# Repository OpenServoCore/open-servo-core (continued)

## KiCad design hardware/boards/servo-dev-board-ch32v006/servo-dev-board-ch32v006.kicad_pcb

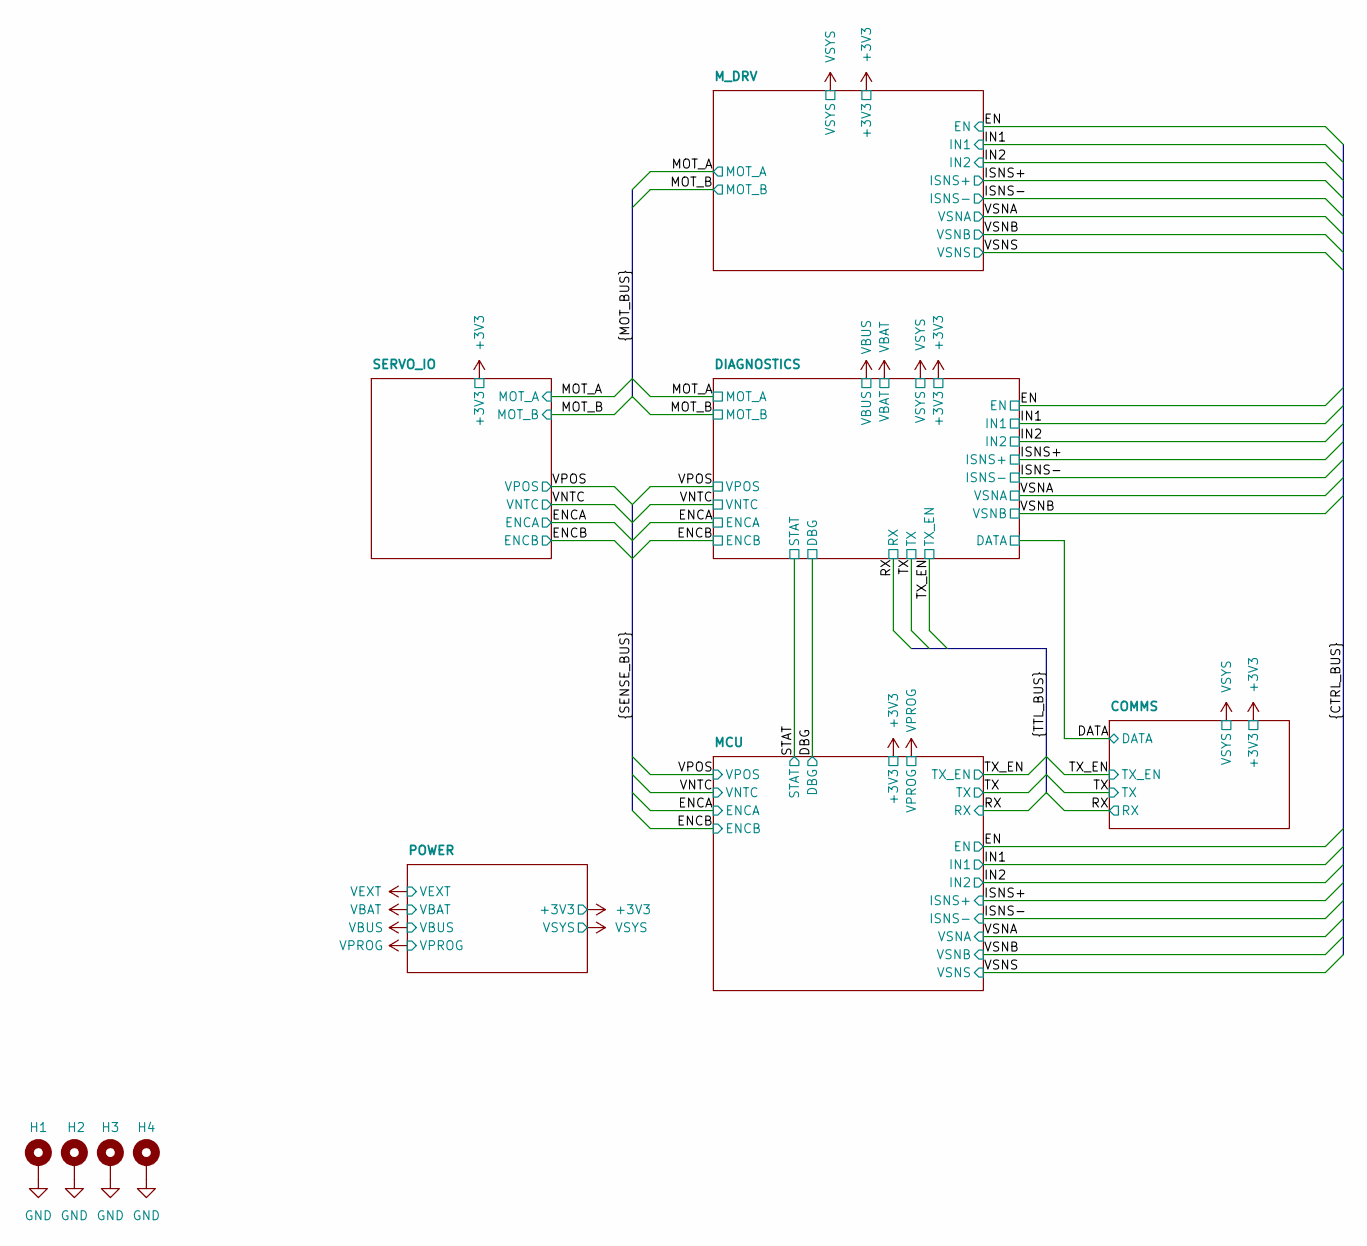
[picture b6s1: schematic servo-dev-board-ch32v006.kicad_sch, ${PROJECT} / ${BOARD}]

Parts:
H1, H2, H3, H4: MountingHole_Pad_MP; MountingHole_2.2mm_M2_ISO7380_Pad

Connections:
GND: H1.1 (1_1), H2.1 (1_1), H3.1 (1_1), H4.1 (1_1); also elsewhere on the board

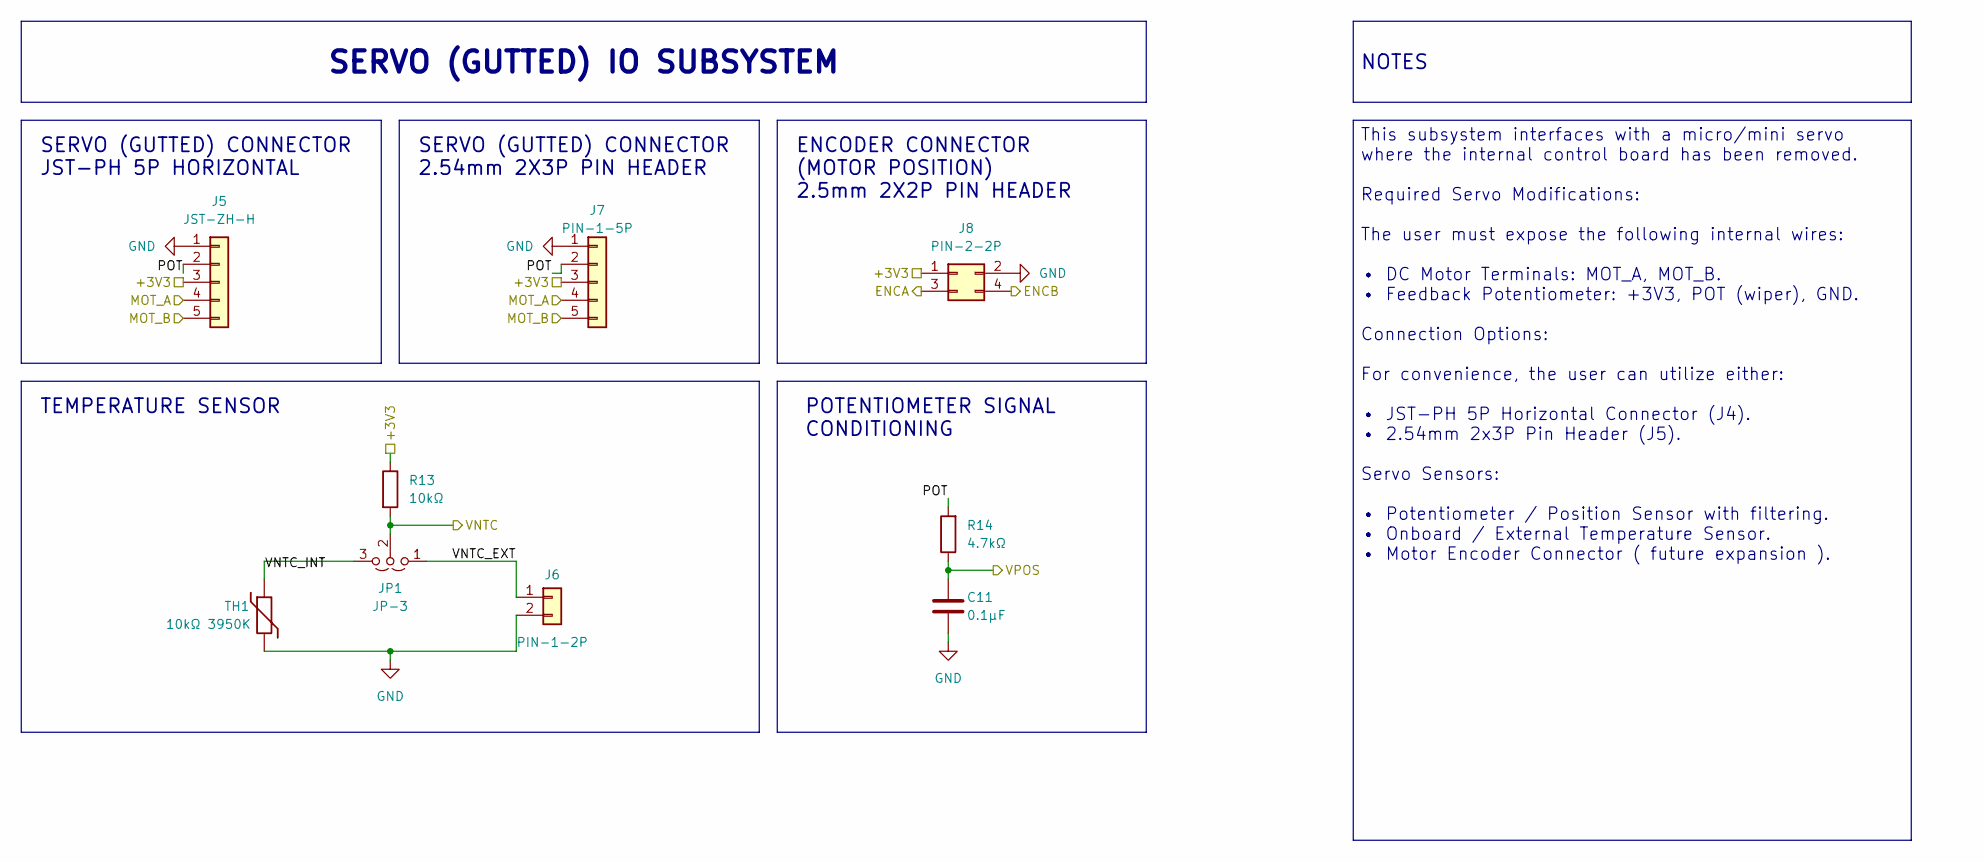
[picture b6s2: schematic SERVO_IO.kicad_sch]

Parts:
C11: 0.1µF; C_0805_2012Metric_Pad1.18x1.45mm_HandSolder; LCSC C28233
J5: JST-ZH-H; CONN-TH_S5B-ZR-LF-SN; JLC Type Extended
J6: PIN-1-2P; PinHeader_1x02_P2.54mm_Vertical; LCSC C492401
J7: PIN-1-5P; PinHeader_1x05_P2.54mm_Vertical; LCSC C42431812
J8: PIN-2-2P; PinHeader_2x02_P2.54mm_Vertical; LCSC C66690
JP1: JP-3; PinHeader_1x03_P2.54mm_Vertical; LCSC C41425293
R13: 10kΩ; R_0805_2012Metric_Pad1.20x1.40mm_HandSolder; LCSC C17414
R14: 4.7kΩ; R_0805_2012Metric_Pad1.20x1.40mm_HandSolder; LCSC C17673
TH1: 10kΩ 3950K; R_0805_2012Metric_Pad1.20x1.40mm_HandSolder; LCSC C95968

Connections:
+3V3: J5.3, J7.3, J8.1, R13.1; also elsewhere on the board
/ENCA: J8.3; also elsewhere on the board
/ENCB: J8.4; also elsewhere on the board
/MOT_A: J5.4, J7.4; also elsewhere on the board
/MOT_B: J5.5, J7.5; also elsewhere on the board
/SERVO_IO/POT: J5.2, J7.2, R14.2
/SERVO_IO/VNTC_EXT: J6.1, JP1.1 (A)
/SERVO_IO/VNTC_INT: JP1.3 (B), TH1.1
/VNTC: JP1.2 (C), R13.2; also elsewhere on the board
/VPOS: C11.1, R14.1; also elsewhere on the board
GND: C11.2, J5.1, J6.2, J7.1, J8.2, TH1.2; also elsewhere on the board

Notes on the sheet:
SERVO (GUTTED) CONNECTOR 2.54mm 2X3P PIN HEADER
ENCODER CONNECTOR (MOTOR POSITION) 2.5mm 2X2P PIN HEADER
TEMPERATURE SENSOR
POTENTIOMETER SIGNAL CONDITIONING
SERVO (GUTTED) CONNECTOR JST-PH 5P HORIZONTAL
This subsystem interfaces with a micro/mini servo where the internal control board has been removed. Required Servo Modifications: The user must expose the following internal wires: • DC Motor Terminals: MOT_A, MOT_B. • Feedback Potentiometer: +3V3, POT (wiper), GND. Connection Options: For conveni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
NOTES
SERVO (GUTTED) IO SUBSYSTEM

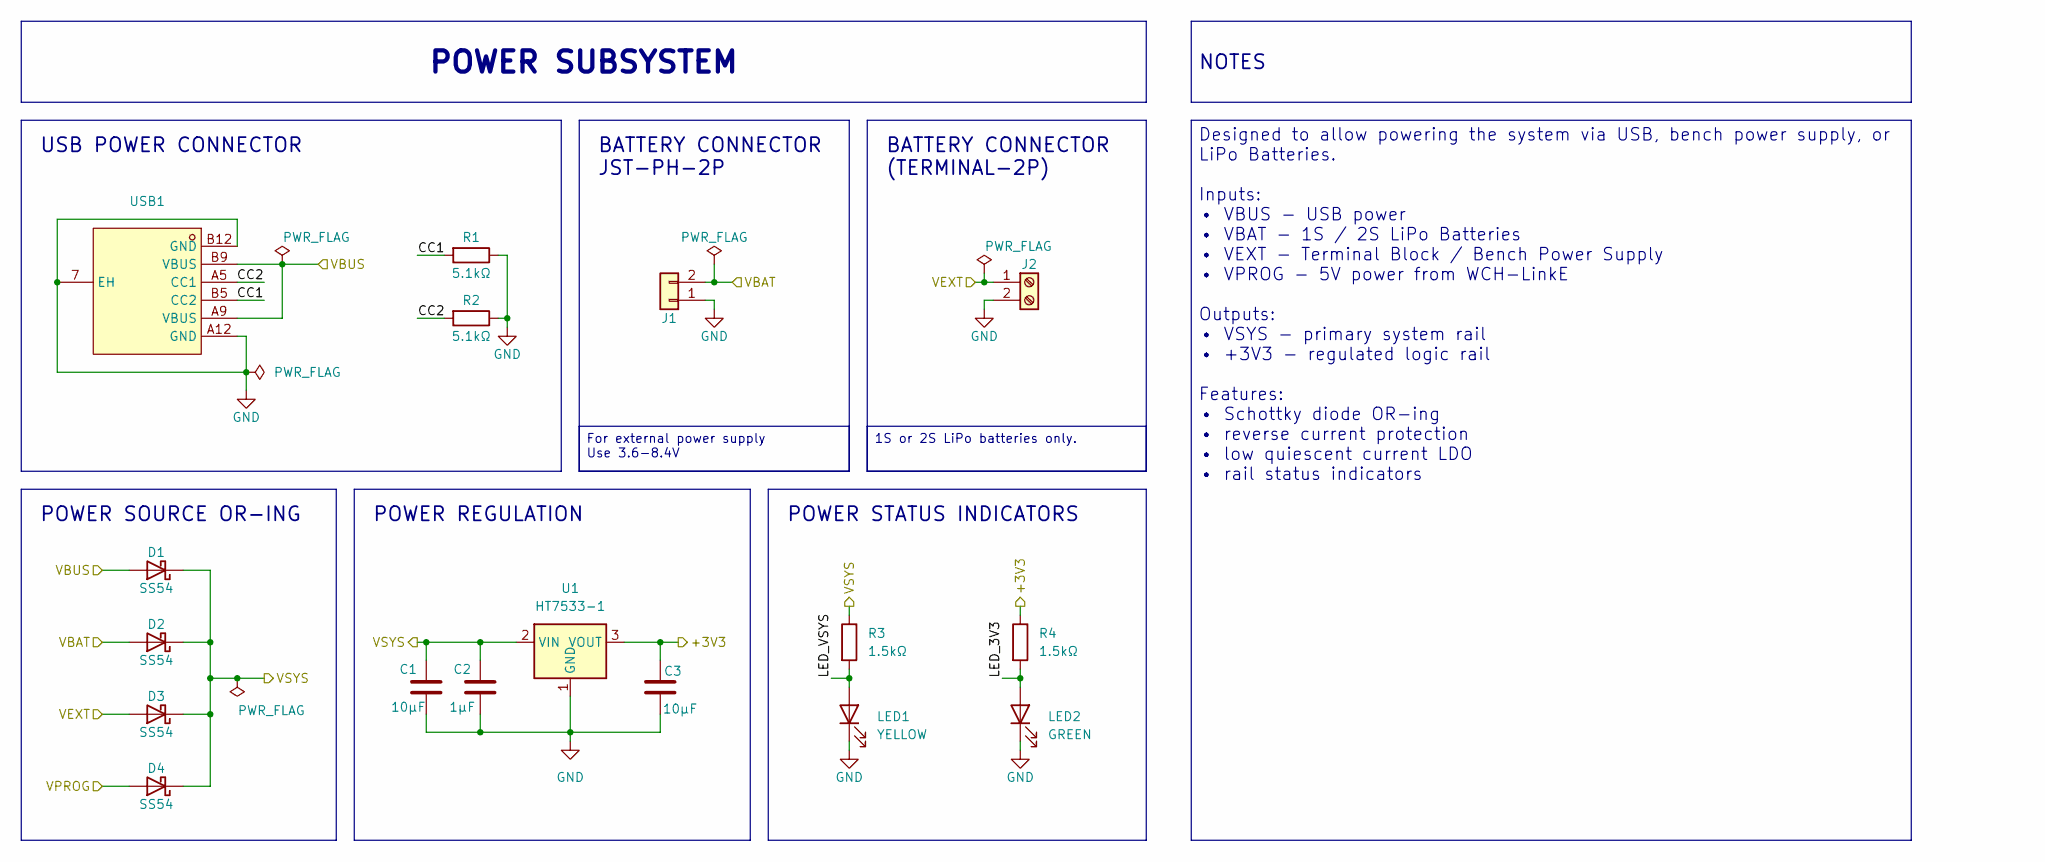
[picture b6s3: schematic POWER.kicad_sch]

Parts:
C1, C3: 10µF; C_0805_2012Metric_Pad1.18x1.45mm_HandSolder; LCSC C440198
C2: 1µF; C_0805_2012Metric_Pad1.18x1.45mm_HandSolder; LCSC C28323
D1, D2, D3, D4: SS54; D_SMA_Handsoldering; LCSC C22452
J1: JST-PH-H; CONN-TH_S2B-PH-K-S-LF-SN; LCSC C173752
J2: TERM; CONN-TH_2P-P5.00_WJ500V-5.08-2P; LCSC C8465
LED1: YELLOW; LED_0805_2012Metric; LCSC C2296
LED2: GREEN; LED_0805_2012Metric; LCSC C2297
R1, R2: 5.1kΩ; R_0805_2012Metric_Pad1.20x1.40mm_HandSolder; LCSC C27834
R3, R4: 1.5kΩ; R_0805_2012Metric_Pad1.20x1.40mm_HandSolder; LCSC C4310
U1: HT7533-1; SOT-89-3_Handsoldering; LCSC C14289
USB1: TYPE-C-H; TYPE-C-SMD_TYPE-C-6P-073; LCSC C668623

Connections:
+3V3: C3.1, R4.1, U1.3 (VOUT); also elsewhere on the board
/POWER/CC1: R1.2, USB1.B5 (CC2)
/POWER/CC2: R2.2, USB1.A5 (CC1)
/POWER/LED_3V3: LED2.2 (A), R4.2
/POWER/LED_VSYS: LED1.2 (A), R3.2
GND: C1.2, C2.2, C3.2, J1.1, J2.2, LED1.1 (K), LED2.1 (K), R1.1, R2.1, U1.1 (GND), USB1.7 (EH), USB1.A12 (GND), USB1.B12 (GND); also elsewhere on the board
VBAT: D2.2 (A), J1.2; also elsewhere on the board
VBUS: D1.2 (A), USB1.A9 (VBUS), USB1.B9 (VBUS); also elsewhere on the board
VEXT: D3.2 (A), J2.1
VPROG: D4.2 (A); also elsewhere on the board
VSYS: C1.1, C2.1, D1.1 (K), D2.1 (K), D3.1 (K), D4.1 (K), R3.1, U1.2 (VIN); also elsewhere on the board

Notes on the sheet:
BATTERY CONNECTOR JST-PH-2P
BATTERY CONNECTOR (TERMINAL-2P)
POWER REGULATION
POWER STATUS INDICATORS
USB POWER CONNECTOR
POWER SOURCE OR-ING
NOTES
Designed to allow powering the system via USB, bench power supply, or LiPo Batteries. Inputs: • VBUS - USB power • VBAT - 1S / 2S LiPo Batteries • VEXT - Terminal Block / Bench Power Supply • VPROG - 5V power from WCH-LinkE Outputs: • VSYS - primary system rail • +3V3 - regulated logic rail Feature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
POWER SUBSYSTEM
For external power supply Use 3.6-8.4V
1S or 2S LiPo batteries only.

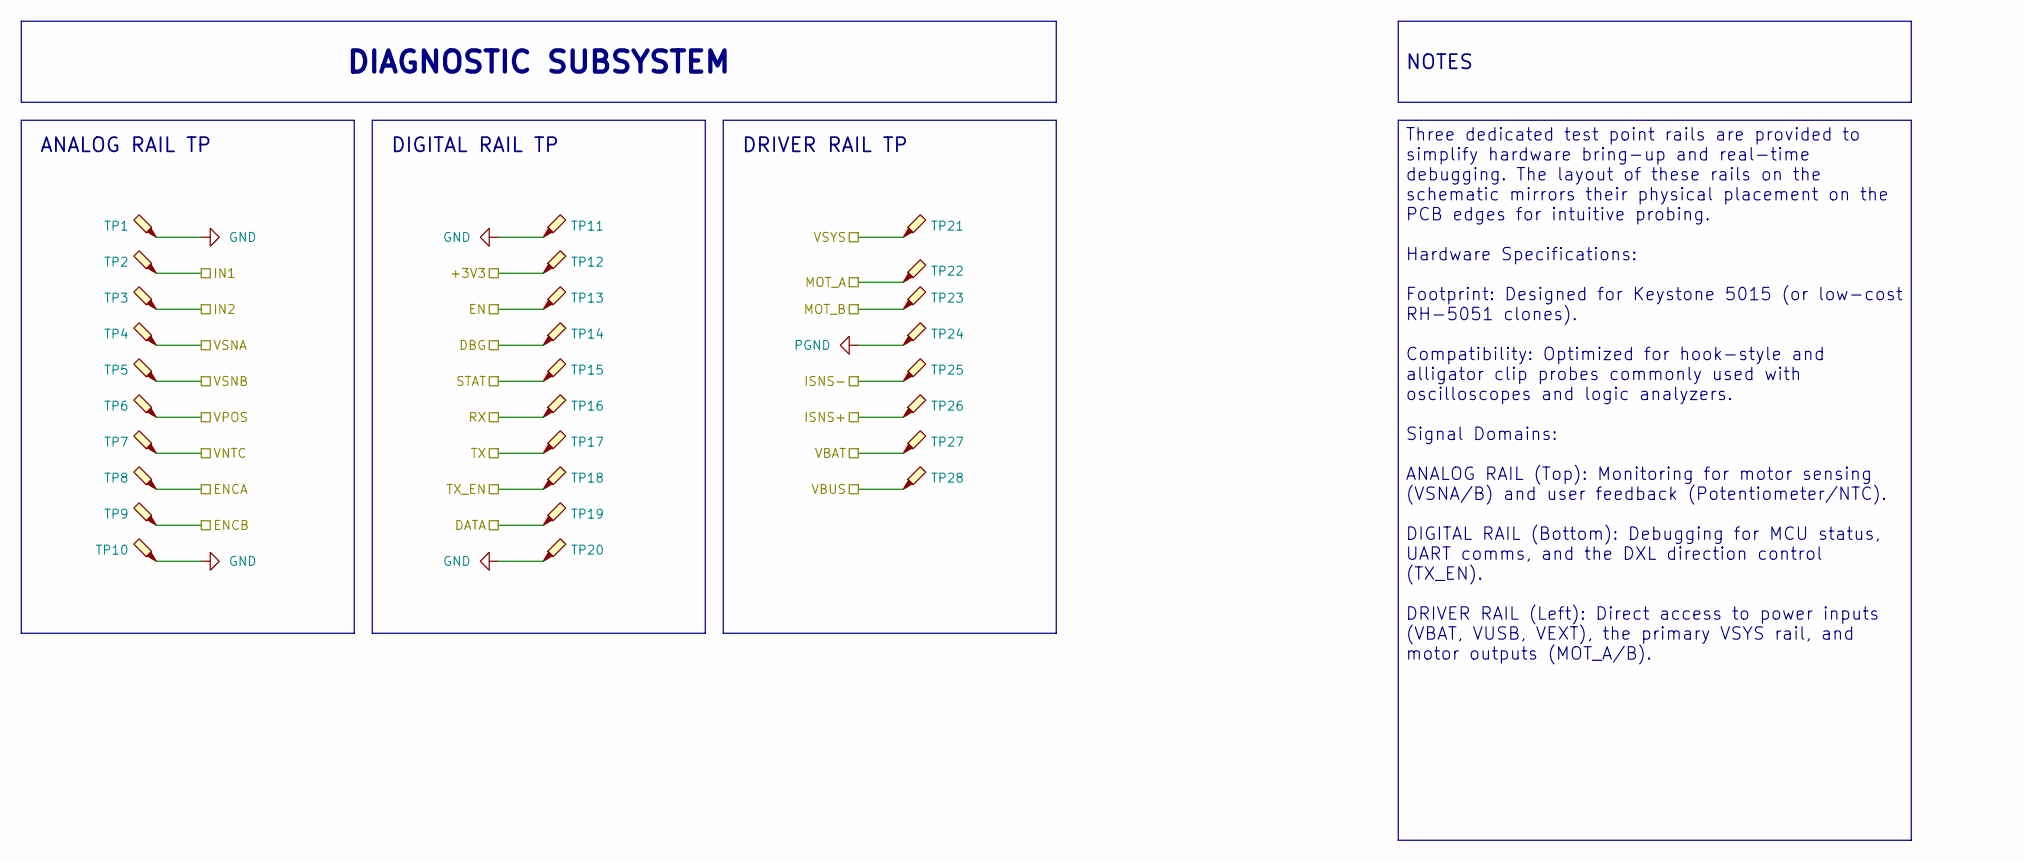
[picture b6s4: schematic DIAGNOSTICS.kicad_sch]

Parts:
TP1, TP2, TP3, TP4, TP5, TP6, TP7, TP8, TP9, TP10, TP11, TP12, TP13, TP14, TP15, TP16, TP17, TP18, TP19, TP20, TP21, TP22, TP23, TP24, TP25, TP26, TP27, TP28: TestPoint_Probe; TestPoint_Keystone_5015_Micro_Mini; LCSC C5199798

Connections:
+3V3: TP12.1 (1_1); also elsewhere on the board
/DATA: TP19.1 (1_1); also elsewhere on the board
/DBG: TP14.1 (1_1); also elsewhere on the board
/EN: TP13.1 (1_1); also elsewhere on the board
/ENCA: TP8.1 (1_1); also elsewhere on the board
/ENCB: TP9.1 (1_1); also elsewhere on the board
/IN1: TP2.1 (1_1); also elsewhere on the board
/IN2: TP3.1 (1_1); also elsewhere on the board
/ISNS+: TP26.1 (1_1); also elsewhere on the board
/ISNS-: TP25.1 (1_1); also elsewhere on the board
/MOT_A: TP22.1 (1_1); also elsewhere on the board
/MOT_B: TP23.1 (1_1); also elsewhere on the board
/RX: TP16.1 (1_1); also elsewhere on the board
/STAT: TP15.1 (1_1); also elsewhere on the board
/TX: TP17.1 (1_1); also elsewhere on the board
/TX_EN: TP18.1 (1_1); also elsewhere on the board
/VNTC: TP7.1 (1_1); also elsewhere on the board
/VPOS: TP6.1 (1_1); also elsewhere on the board
/VSNA: TP4.1 (1_1); also elsewhere on the board
/VSNB: TP5.1 (1_1); also elsewhere on the board
GND: TP1.1 (1_1), TP10.1 (1_1), TP11.1 (1_1), TP20.1 (1_1); also elsewhere on the board
PGND: TP24.1 (1_1); also elsewhere on the board
VBAT: TP27.1 (1_1); also elsewhere on the board
VBUS: TP28.1 (1_1); also elsewhere on the board
VSYS: TP21.1 (1_1); also elsewhere on the board

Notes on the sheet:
ANALOG RAIL TP
DRIVER RAIL TP
DIGITAL RAIL TP
DIAGNOSTIC SUBSYSTEM
NOTES
Three dedicated test point rails are provided to simplify hardware bring-up and real-time debugging. The layout of these rails on the schematic mirrors their physical placement on the PCB edges for intuitive probing. Hardware Specifications: Footprint: Designed for Keystone 5015 (or low-cost RH-505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

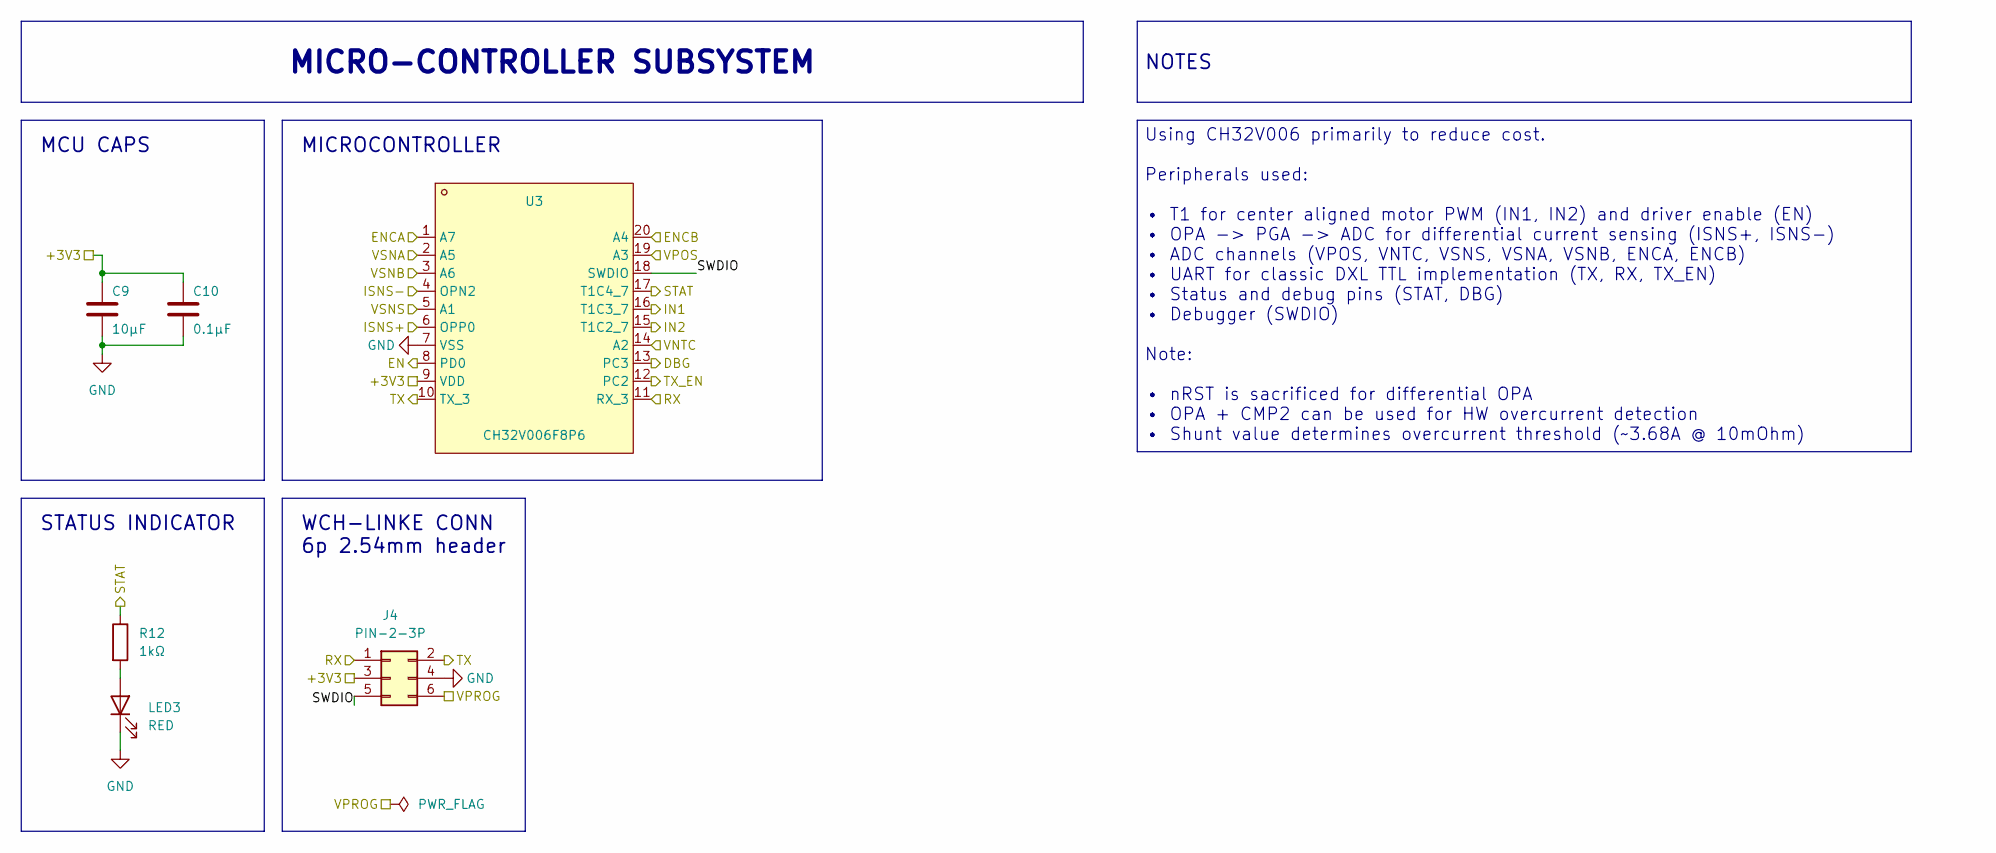
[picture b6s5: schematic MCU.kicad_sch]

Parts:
C9: 10µF; C_0805_2012Metric_Pad1.18x1.45mm_HandSolder; LCSC C440198
C10: 0.1µF; C_0805_2012Metric_Pad1.18x1.45mm_HandSolder; LCSC C28233
J4: PIN-2-3P; PinHeader_2x03_P2.54mm_Vertical; LCSC C65114
LED3: RED; LED_0805_2012Metric; LCSC C84256
R12: 1kΩ; R_0805_2012Metric_Pad1.20x1.40mm_HandSolder; LCSC C17513
U3: CH32V006F8P6; TSSOP-20_4.4x6.5mm_P0.65mm; LCSC C52753342

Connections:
+3V3: C9.1, C10.1, J4.3, U3.9 (VDD); also elsewhere on the board
/DBG: U3.13 (PC3); also elsewhere on the board
/EN: U3.8 (PD0); also elsewhere on the board
/ENCA: U3.1 (A7); also elsewhere on the board
/ENCB: U3.20 (A4); also elsewhere on the board
/IN1: U3.16 (T1C3_7); also elsewhere on the board
/IN2: U3.15 (T1C2_7); also elsewhere on the board
/ISNS+: U3.6 (OPP0); also elsewhere on the board
/ISNS-: U3.4 (OPN2); also elsewhere on the board
/MCU/SWDIO: J4.5, U3.18 (SWDIO)
/RX: J4.1, U3.11 (RX_3); also elsewhere on the board
/STAT: R12.1, U3.17 (T1C4_7); also elsewhere on the board
/TX: J4.2, U3.10 (TX_3); also elsewhere on the board
/TX_EN: U3.12 (PC2); also elsewhere on the board
/VNTC: U3.14 (A2); also elsewhere on the board
/VPOS: U3.19 (A3); also elsewhere on the board
/VSNA: U3.2 (A5); also elsewhere on the board
/VSNB: U3.3 (A6); also elsewhere on the board
/VSNS: U3.5 (A1); also elsewhere on the board
GND: C9.2, C10.2, J4.4, LED3.1 (K), U3.7 (VSS); also elsewhere on the board
unnamed: LED3.2 (A), R12.2
VPROG: J4.6; also elsewhere on the board

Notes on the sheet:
MCU CAPS
MICROCONTROLLER
STATUS INDICATOR
WCH-LINKE CONN 6p 2.54mm header
NOTES
Using CH32V006 primarily to reduce cost. Peripherals used: • T1 for center aligned motor PWM (IN1, IN2) and driver enable (EN) • OPA -> PGA -> ADC for differential current sensing (ISNS+, ISNS-) • ADC channels (VPOS, VNTC, VSNS, VSNA, VSNB, ENCA, ENCB) • UART for classic DXL TTL implementation (TX,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
MICRO-CONTROLLER SUBSYSTEM

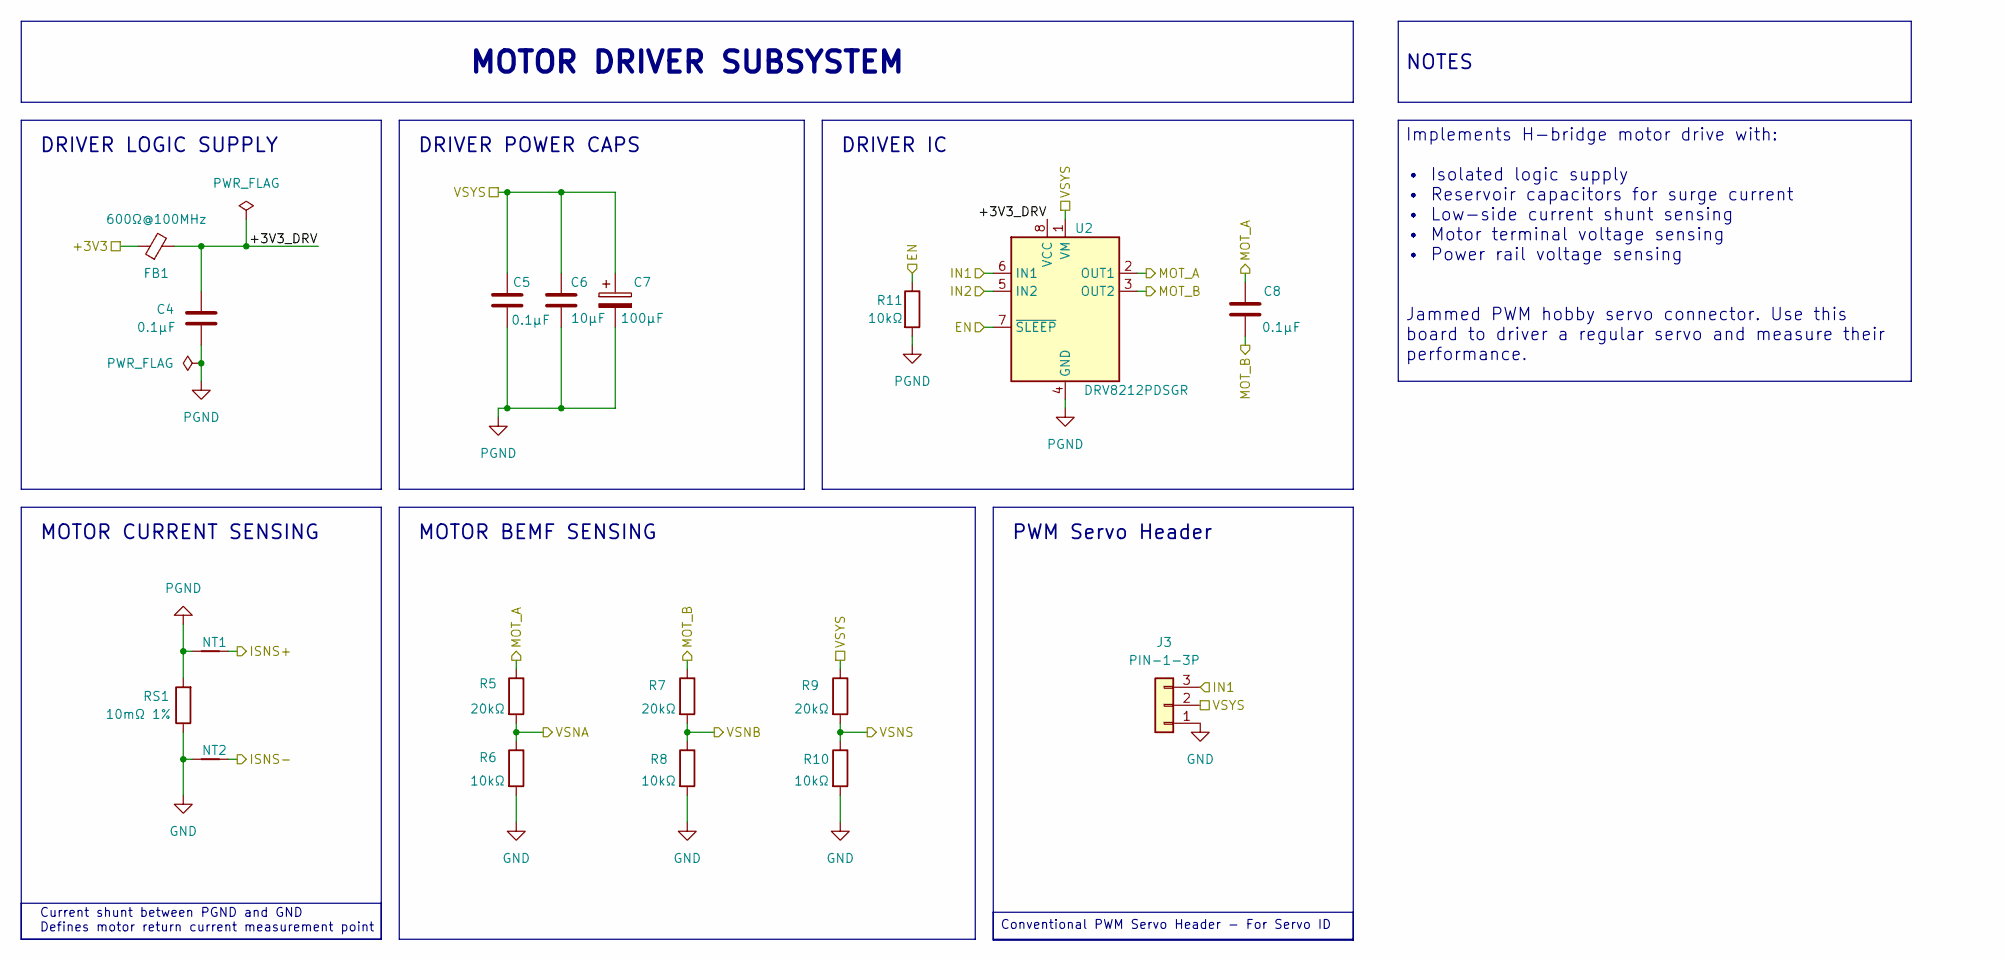
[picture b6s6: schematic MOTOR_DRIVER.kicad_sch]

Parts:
C4, C5, C8: 0.1µF; C_0805_2012Metric_Pad1.18x1.45mm_HandSolder; LCSC C28233
C6: 10µF; C_0805_2012Metric_Pad1.18x1.45mm_HandSolder; LCSC C440198
C7: 100µF; CP_Elec_6.3x5.4; LCSC C19271225
FB1: 600Ω@100MHz; L_0805_2012Metric_Pad1.05x1.20mm_HandSolder; LCSC C1017
J3: PIN-1-3P; PinHeader_1x03_P2.54mm_Vertical; LCSC C49257
NT1, NT2: NetTie_2; NetTie-2_SMD_0.2mm
R5, R7, R9: 20kΩ; R_0805_2012Metric_Pad1.20x1.40mm_HandSolder; LCSC C4328
R6, R8, R10, R11: 10kΩ; R_0805_2012Metric_Pad1.20x1.40mm_HandSolder; LCSC C17414
RS1: 10mΩ 1%; R_1206_3216Metric; LCSC C473031
U2: DRV8212PDSGR; WSON-8-1EP_2x2mm_P0.5mm_EP0.9x1.6mm; LCSC C5208051

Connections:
+3V3: FB1.1; also elsewhere on the board
/EN: R11.1, U2.7 (~SLEEP); also elsewhere on the board
/IN1: J3.3, U2.6 (IN1); also elsewhere on the board
/IN2: U2.5 (IN2); also elsewhere on the board
/ISNS+: NT1.1; also elsewhere on the board
/ISNS-: NT2.1; also elsewhere on the board
/MOT_A: C8.1, R5.1, U2.2 (OUT1); also elsewhere on the board
/MOT_B: C8.2, R7.1, U2.3 (OUT2); also elsewhere on the board
/M_DRV/+3V3_DRV: C4.1, FB1.2, U2.8 (VCC)
/VSNA: R5.2, R6.1; also elsewhere on the board
/VSNB: R7.2, R8.1; also elsewhere on the board
/VSNS: R9.2, R10.1; also elsewhere on the board
GND: J3.1, NT2.2, R6.2, R8.2, R10.2, RS1.1; also elsewhere on the board
PGND: C4.2, C5.2, C6.2, C7.2, NT1.2, R11.2, RS1.2, U2.4 (GND), U2.9 (GND); also elsewhere on the board
VSYS: C5.1, C6.1, C7.1, J3.2, R9.1, U2.1 (VM); also elsewhere on the board

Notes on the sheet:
MOTOR BEMF SENSING
Current shunt between PGND and GND Defines motor return current measurement point
DRIVER POWER CAPS
PWM Servo Header
DRIVER LOGIC SUPPLY
MOTOR CURRENT SENSING
DRIVER IC
Conventional PWM Servo Header - For Servo ID
MOTOR DRIVER SUBSYSTEM
NOTES
Implements H-bridge motor drive with: • Isolated logic supply • Reservoir capacitors for surge current • Low-side current shunt sensing • Motor terminal voltage sensing • Power rail voltage sensing Jammed PWM hobby servo connector. Use this board to driver a regular servo and measure their performa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

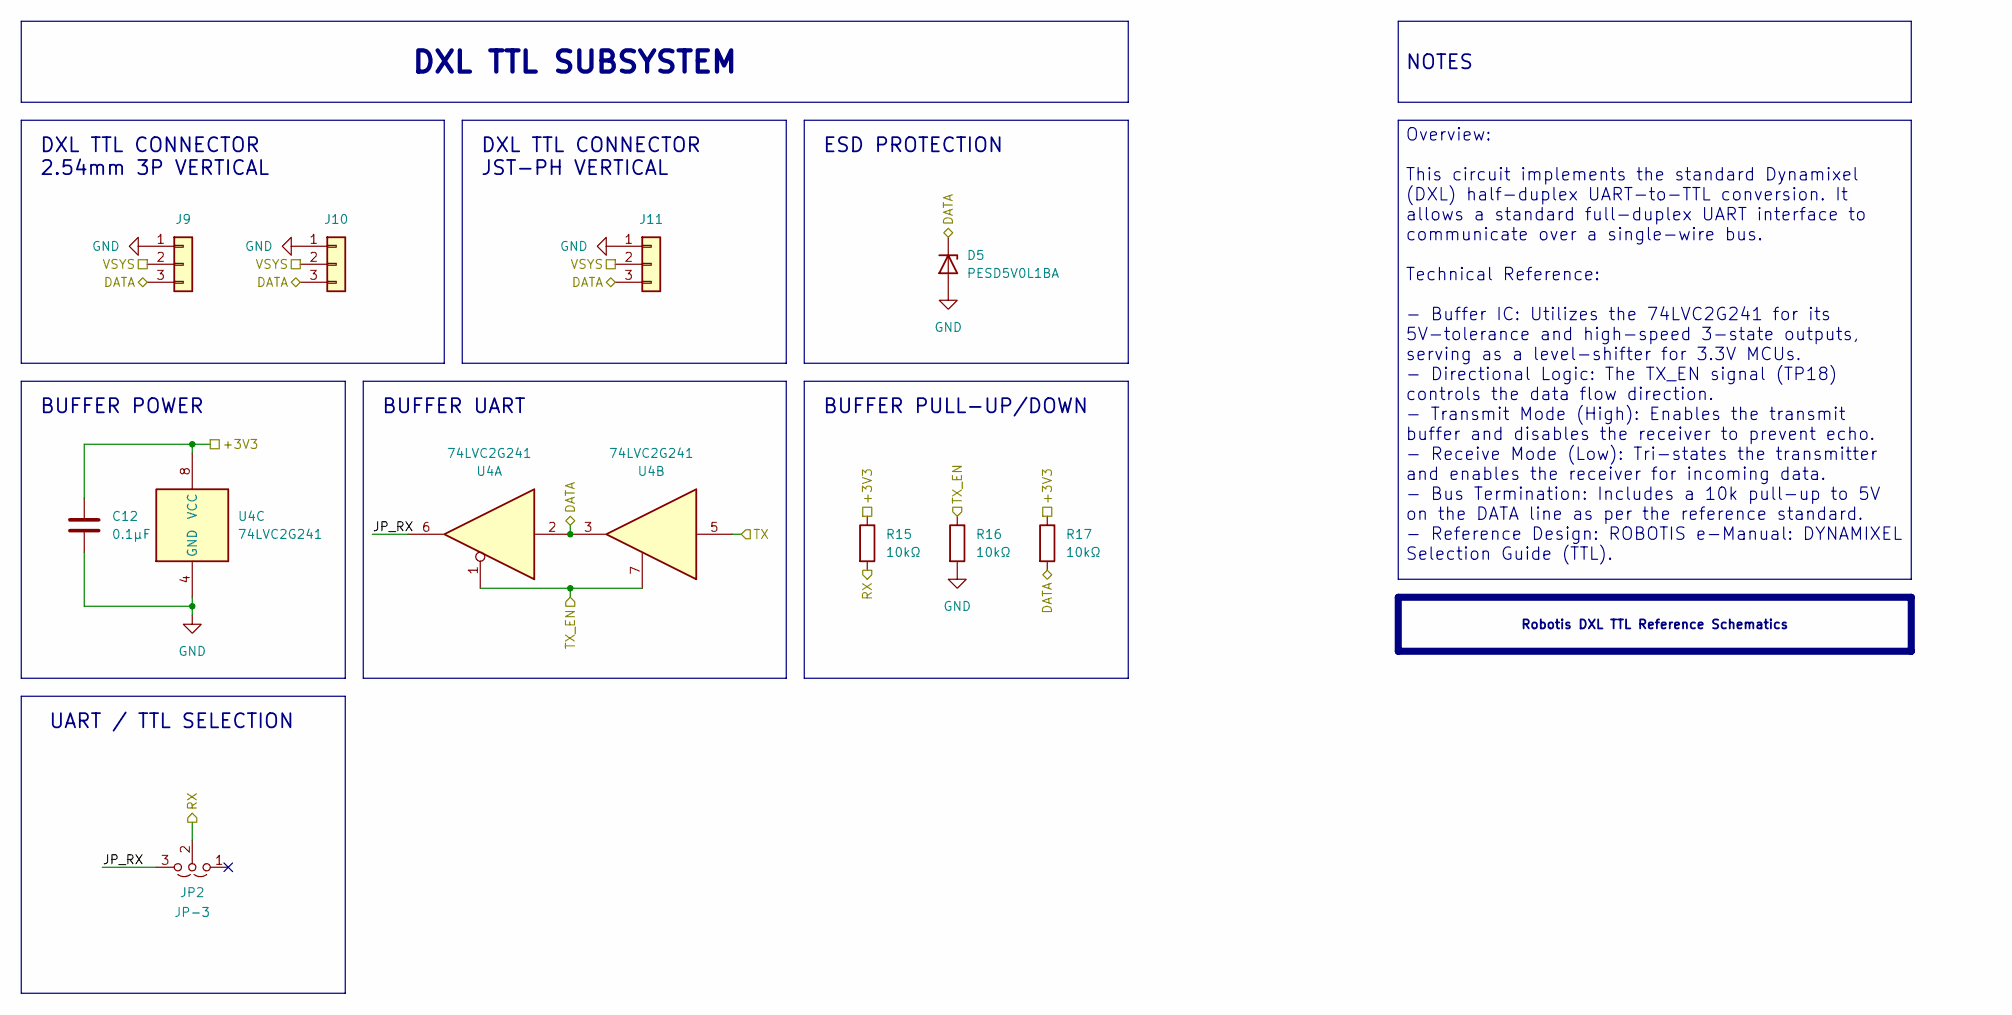
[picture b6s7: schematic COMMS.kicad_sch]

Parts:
C12: 0.1µF; C_0805_2012Metric_Pad1.18x1.45mm_HandSolder; LCSC C28233
D5: PESD5V0L1BA; D_SOD-323_HandSoldering; LCSC C2687118
J9, J10: PIN-1-3P; PinHeader_1x03_P2.54mm_Vertical; LCSC C49257
J11: JST-PH-V; CONN-TH_B3B-PH-K-S; JLC Type Extended
JP2: JP-3; PinHeader_1x03_P2.54mm_Vertical; LCSC C41425293
R15, R16, R17: 10kΩ; R_0805_2012Metric_Pad1.20x1.40mm_HandSolder; LCSC C17414
U4: 74LVC2G241; VSSOP-8_L2.3-W2.0-P0.50-LS3.1-BR; LCSC C10430

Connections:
+3V3: C12.1, R15.1, R17.1, U4.8 (VCC); also elsewhere on the board
/COMMS/JP_RX: JP2.3 (B), U4.6
/DATA: D5.1 (K), J9.3, J10.3, J11.3, R17.2, U4.2, U4.3; also elsewhere on the board
/RX: JP2.2 (C), R15.2; also elsewhere on the board
/TX: U4.5; also elsewhere on the board
/TX_EN: R16.1, U4.1, U4.7; also elsewhere on the board
GND: C12.2, D5.2 (A), J9.1, J10.1, J11.1, R16.2, U4.4 (GND); also elsewhere on the board
VSYS: J9.2, J10.2, J11.2; also elsewhere on the board

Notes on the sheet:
ESD PROTECTION
BUFFER UART
BUFFER PULL-UP/DOWN
DXL TTL CONNECTOR JST-PH VERTICAL
BUFFER POWER
UART / TTL SELECTION
DXL TTL CONNECTOR 2.54mm 3P VERTICAL
Overview: This circuit implements the standard Dynamixel (DXL) half-duplex UART-to-TTL conversion. It allows a standard full-duplex UART interface to communicate over a single-wire bus. Technical Reference: - Buffer IC: Utilizes the 74LVC2G241 for its 5V-tolerance and high-speed 3-state outputs, se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
DXL TTL SUBSYSTEM
Robotis DXL TTL Reference Schematics
NOTES

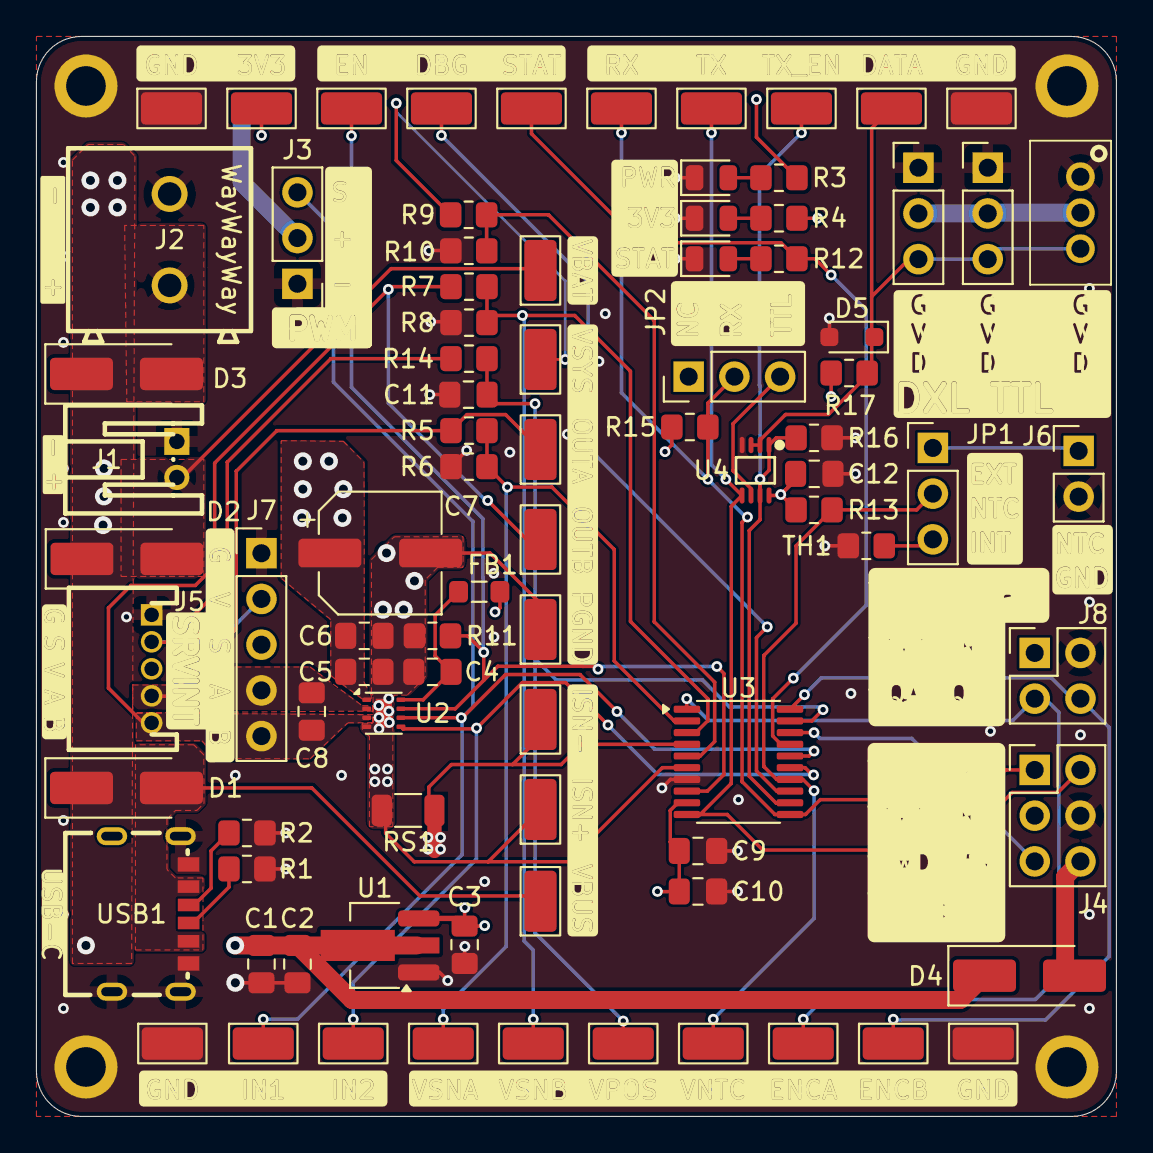
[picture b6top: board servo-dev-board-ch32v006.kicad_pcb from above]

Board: 4 copper layers, 60.0 x 60.0 mm, 92 parts (0 on the bottom side), 39 nets.
